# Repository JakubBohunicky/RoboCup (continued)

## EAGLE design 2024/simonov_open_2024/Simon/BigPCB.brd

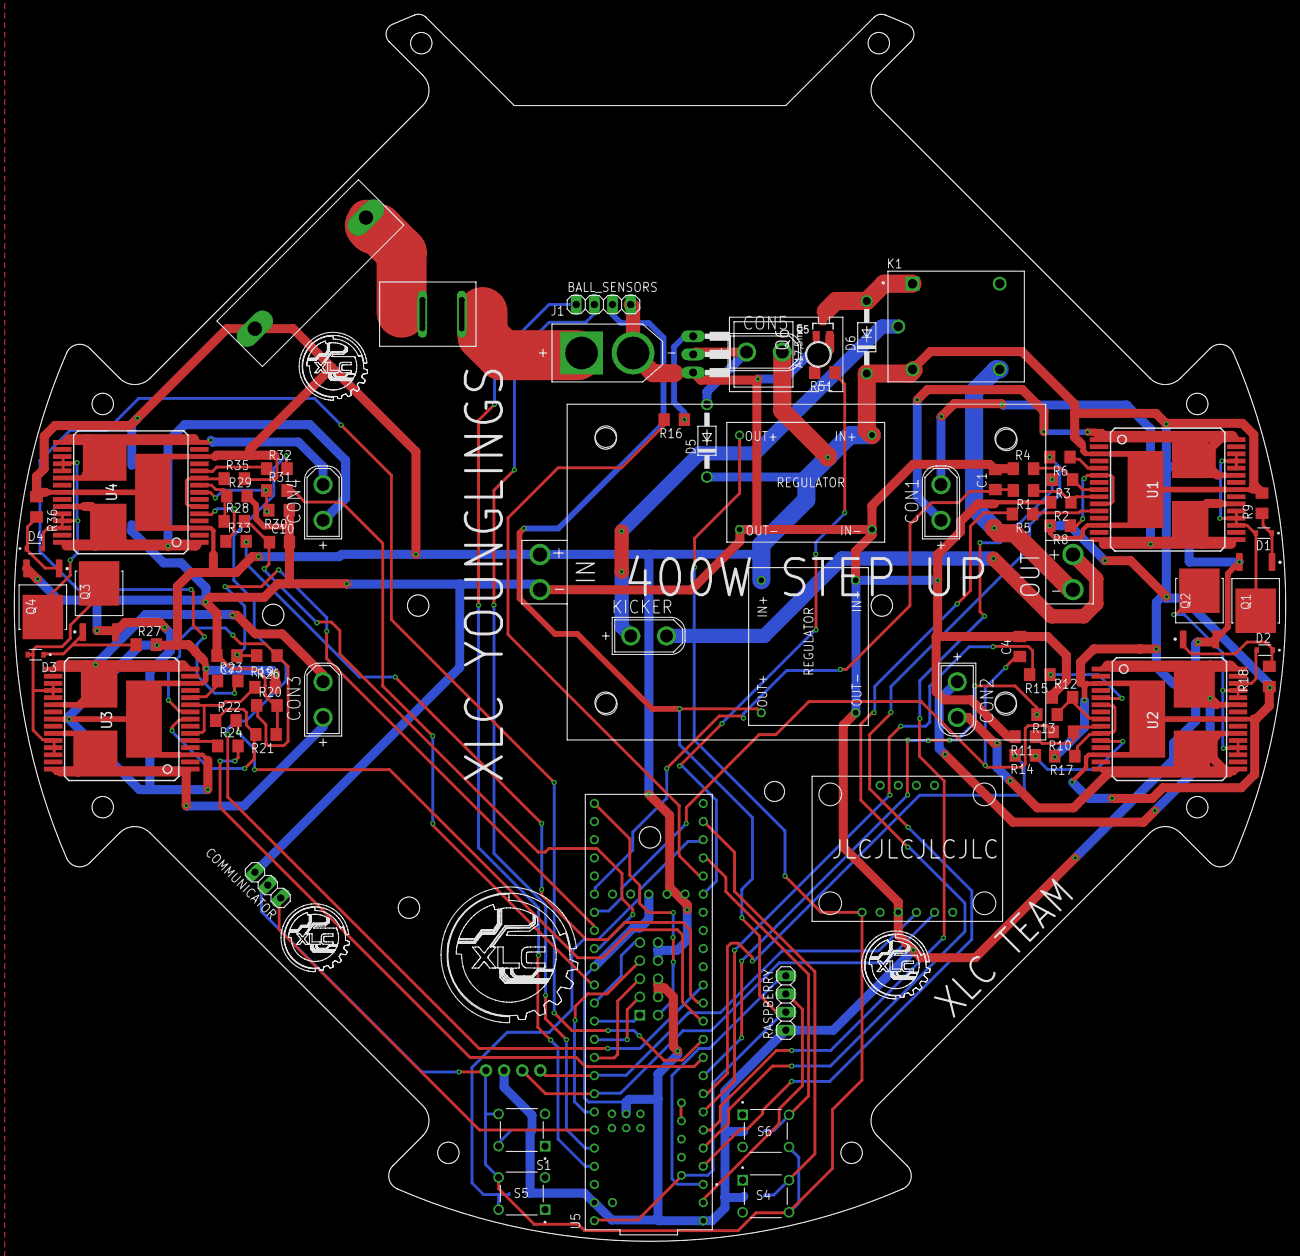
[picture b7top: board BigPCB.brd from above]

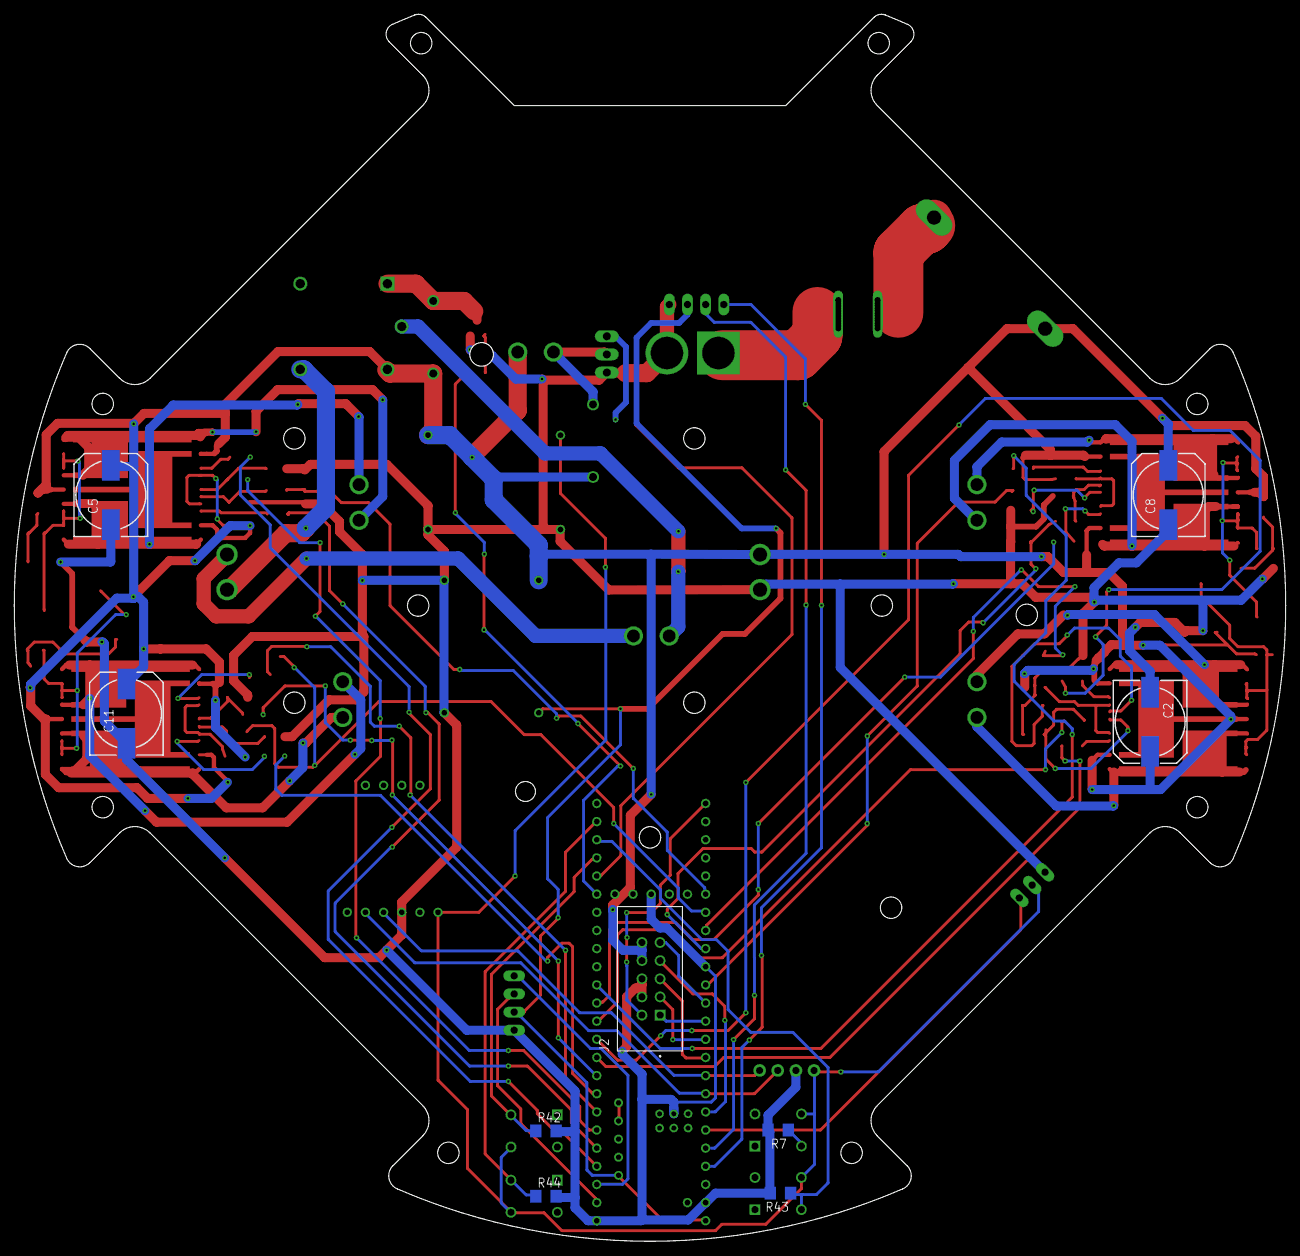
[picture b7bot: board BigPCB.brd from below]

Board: 2 copper layers, 178.0 x 171.8 mm, 86 parts (9 on the bottom side), 85 nets.

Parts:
3.3V, 5V: MP1584EN_REGULATOR
BALL_SENSORS: 1X04
C1, C4, C7, C10: 33nF; C1206
C2, C5, C8, C11: 470uF; 150CLZ-1014
COMMUNICATOR: 1X03
CON1, CON2, CON3, CON4, CON5: XT30UPB-M
D1, D2, D3, D4: BZT52C3V6S_RRG; DIO_BZT52C3V6S_RRG
D5, D6: 1N4004; DO41-10
J1: XT60-M; AMASS_XT60-M
J2: SBH11-PBPC-D05-ST-BK; SULLINS_SBH11-PBPC-D05-ST-BK
K1: SRD-05VDC-SL-C; RELAY_SRD-05VDC-SL-C
KICKER: XT30UPB-M
Q1, Q2, Q3, Q4: FDD8580
Q5: MMBT2222; SOT23-BEC
Q6: TIP120; TO220AH
R1, R4, R10, R12, R19, R21, R28, R30: 10k; R1206
R2, R11, R20, R29: 1.5k; R1206
R3, R5, R6, R13, R14, R15, R22, R23, R24, R31, R32, R33, R51: 1k; R1206
R7, R42, R43, R44: 10K; R1206
R8, R17, R26, R35: 4.7k; R1206
R9, R18, R27, R36: 100k; R1206
R16: 2.2k; R1206
RASPBERRY: 1X04
S1, S4, S5, S6: TS02-66-60-BK-100-LCR-D; SW_TS02-66-60-BK-100-LCR-D
U1, U2, U3, U4: VNH2SP30; MULTIPOWER30
U5: DEV-16771; MODULE_DEV-16771
U$1: BNO055_ADAFRUIT; BNO055
U$2: OLED_0.96_I2C
U$3: 1015_SWITHC; 10*15_SWITCH
U$4: BLX-A_FUSE_HOLDER
U$10: 400W_STEP_UP

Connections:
3.3V: 3.3V.P$2, COMMUNICATOR.2, S1.4, S4.4, S5.4, S6.4, U5.3.3V_1, U5.3.3V_2, U5.3.3V_3, U$1.VIN, U$2.VCC
5V: 5V.P$2, BALL_SENSORS.3, RASPBERRY.2, U5.5V, U5.VIN
12V: 3.3V.P$1, 5V.P$1, C2.+, C5.+, C8.+, C11.+, CON5.-, D5.C, D6.C, J2.8, J2.10, K1.A2, R8.2, R9.2, R17.2, R18.2, R26.2, R27.2, R35.2, R36.2, U1.P$3, U1.P$13, U1.P$23, U2.P$3, U2.P$13, U2.P$23, U3.P$3, U3.P$13, U3.P$23, U4.P$3, U4.P$13, U4.P$23, U$4.P$2, U$10.P$2
COMMUNICATOR: COMMUNICATOR.1, U5.21
CS_MA: C1.1, R1.2, U5.38
CS_MB: C4.1, R10.2, U5.39
CS_MC: C7.1, R19.2, U5.40
CS_MD: C10.1, R28.2, U5.41
DRIBLLER_IN: R16.2, U5.28
FS1: BALL_SENSORS.2, U5.22
FS2: BALL_SENSORS.1, U5.23
GND: 3.3V.P$3, 3.3V.P$4, 5V.P$3, 5V.P$4, BALL_SENSORS.4, C1.2, C2.-, C4.2, C5.-, C7.2, C8.-, C10.2, C11.-, COMMUNICATOR.3, J1.N, J2.4, J2.6, Q1.3, Q2.3, Q3.3, Q4.3, Q5.E, Q6.E, R2.2, R4.1, R7.2, R11.2, R12.1, R20.2, R21.1, R29.2, R30.1, R42.2, R43.2, R44.2, RASPBERRY.1, U5.GND1, U5.GND2, U5.GND3, U5.GND4, U5.GND5, U$1.GND, U$2.GND, U$10.P$1
IN_A_MA: R6.2, U5.2
IN_A_MB: R15.2, U5.5
IN_A_MC: R24.2, U5.8
IN_A_MD: R33.2, U5.11
IN_B_MA: R5.2, U5.3
IN_B_MB: R14.2, U5.6
IN_B_MC: R23.2, U5.9
IN_B_MD: R32.2, U5.12
KICKER_IN: R51.1, U5.27
LEDS_OUT: J2.2, U5.33
MA_OUT: CON1.+, U1.P$1, U1.P$25, U1.P$30
MA_OUT2: CON1.-, U1.P$15, U1.P$16, U1.P$21
MB_OUT: CON2.+, U2.P$1, U2.P$25, U2.P$30
MB_OUT2: CON2.-, U2.P$15, U2.P$16, U2.P$21
MC_OUT: CON3.+, U3.P$1, U3.P$25, U3.P$30
MC_OUT2: CON3.-, U3.P$15, U3.P$16, U3.P$21
MD_OUT: CON4.+, U4.P$1, U4.P$25, U4.P$30
MD_OUT2: CON4.-, U4.P$15, U4.P$16, U4.P$21
MULTIPLEXER_IN_1: J2.1, U5.15
MULTIPLEXER_IN_2: J2.3, U5.16
MULTIPLEXER_IN_3: J2.5, U5.17
MULTIPLEXER_IN_4: J2.7, U5.20
MULTIPLEXER_OUT: J2.9, U5.14
unnamed: R1.1, R2.1, U1.P$9
unnamed: R5.1, U1.P$11
unnamed: R3.1, R4.2, U1.P$8
unnamed: R6.1, U1.P$5
unnamed: R8.1, U1.P$6, U1.P$10
unnamed: D1.C, Q1.1, R9.1
unnamed: D1.A, Q1.2, U1.P$18, U1.P$19, U1.P$20, U1.P$26, U1.P$27, U1.P$28
unnamed: R10.1, R11.1, U2.P$9
unnamed: R12.2, R13.1, U2.P$8
unnamed: R14.1, U2.P$11
unnamed: R15.1, U2.P$5
unnamed: R17.1, U2.P$6, U2.P$10
unnamed: D2.A, Q2.2, U2.P$18, U2.P$19, U2.P$20, U2.P$26, U2.P$27, U2.P$28
unnamed: D2.C, Q2.1, R18.1
unnamed: R19.1, R20.1, U3.P$9
unnamed: R21.2, R22.1, U3.P$8
unnamed: R23.1, U3.P$11
unnamed: R24.1, U3.P$5
unnamed: R26.1, U3.P$6, U3.P$10
unnamed: D3.A, Q3.2, U3.P$18, U3.P$19, U3.P$20, U3.P$26, U3.P$27, U3.P$28
unnamed: D3.C, Q3.1, R27.1
unnamed: R28.1, R29.1, U4.P$9
unnamed: R30.2, R31.1, U4.P$8
unnamed: R32.1, U4.P$11
unnamed: R33.1, U4.P$5
unnamed: R35.1, U4.P$6, U4.P$10
unnamed: D4.A, Q4.2, U4.P$18, U4.P$19, U4.P$20, U4.P$26, U4.P$27, U4.P$28
unnamed: D4.C, Q4.1, R36.1
unnamed: Q6.B, R16.1
unnamed: J1.P, U$3.P1, U$3.P2, U$3.P3, U$3.P4, U$3.P5, U$3.P6, U$3.P7, U$3.P8, U$3.P9, U$3.P10, U$3.P11, U$3.P12, U$3.P13
unnamed: U$3.P15, U$3.P16, U$3.P17, U$3.P18, U$3.P19, U$3.P20, U$3.P21, U$3.P22, U$3.P23, U$3.P24, U$3.P25, U$3.P26, U$3.P27, U$3.P28, U$4.P$1
unnamed: CON5.+, D5.A, Q6.C
unnamed: KICKER.-, U$10.P$4
unnamed: K1.COM, KICKER.+
unnamed: Q5.B, R51.2
unnamed: K1.NO, U$10.P$3
unnamed: D6.A, K1.A1, Q5.C
PWM_MA: R3.2, U5.4
PWM_MB: R13.2, U5.7
PWM_MC: R22.2, U5.10
PWM_MD: R31.2, U5.13
RX: RASPBERRY.3, U5.0
SCL: U5.19, U$1.SCL, U$2.SCL
SDA: U5.18, U$1.SDA, U$2.SDA
SWITCH_OUT_1: R42.1, S6.2, U5.29
SWITCH_OUT_2: R43.1, S5.2, U5.30
SWITCH_OUT_3: R44.1, S4.2, U5.31
SWITCH_OUT_4: R7.1, S1.2
TX: RASPBERRY.4, U5.1
USB_GND: U5.USB_GND1, U5.USB_GND2

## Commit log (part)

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2023-08-26 schematic
2023-08-27 eagle
2024-03-29 zipka su uzasne
2024-03-29 tsop
2024-04-02 tsopV1
2024-04-21 diera
2024-04-24 LOGO
2024-07-13 code
2024-07-15 poster
2024-07-18 Code V7
2026-01-28 diddyCodeV1_done
2026-01-30 escon
2026-02-19 btns
2026-02-22 pici
2026-02-24 display
2026-02-26 disp
2026-02-28 soccer_menu
2026-02-28 menucko
2026-03-01 HTU21
2026-03-02 attack
2026-03-13 ball
2026-03-31 comms
2026-04-01 controller
2026-05-22 uhdfh
2026-06-23 2pixy
